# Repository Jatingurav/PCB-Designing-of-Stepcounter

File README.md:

# PCB-Designing-of-Stepcounter
I have created the circuit diagram for a Step Counter system, integrating ATtiny85 IC with MPU6050 Accelerometer & Gyroscope, and an OLED Display Module. I have developed a Multi-Layer PCB layout and developed the footprints of the components and generated Gerber files using KiCad software.

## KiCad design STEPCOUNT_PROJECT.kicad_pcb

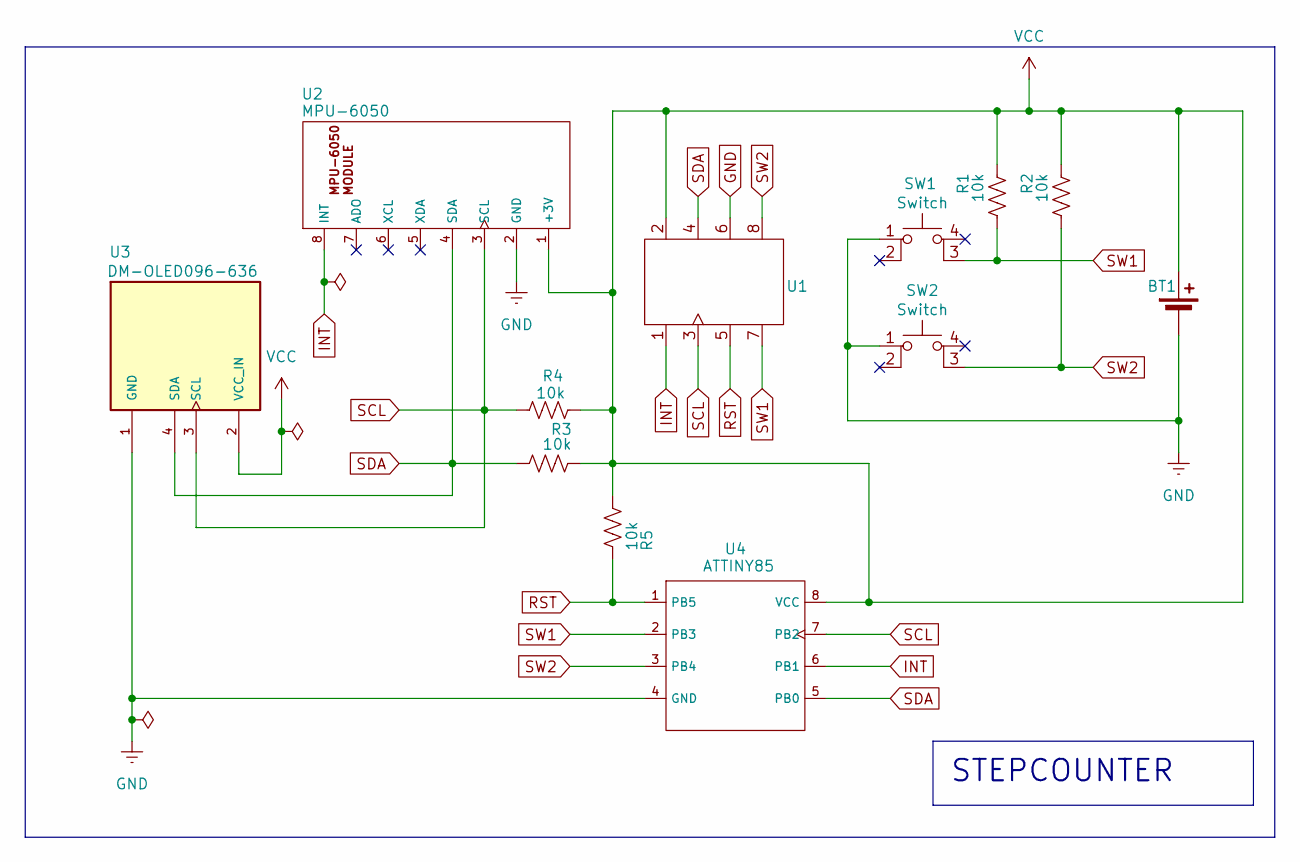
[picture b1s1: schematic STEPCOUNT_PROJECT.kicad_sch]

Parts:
BT1: Battery_Cell; Battery_Panasonic_CR2032-HFN_Horizontal_CircularHoles
R1, R2, R3, R4, R5: 10k; R_Axial_DIN0204_L3.6mm_D1.6mm_P1.90mm_Vertical
SW1, SW2: Switch; Push_E-Switch_KS01Q01
U1: HEADER
U2: MPU-6050; MPU-6050_MODULE
U3: DM-OLED096-636; OLED_DISPLAY; PARTREV 2018-09-10
U4: ATTINY85; ATTINY85_MODULE

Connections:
GND: BT1.2 (-), SW1.1, SW2.1, U1.6, U2.2 (GND), U3.1 (GND), U4.4 (GND)
INT: U1.1, U2.8 (INT), U4.6 (PB1)
RST: R5.2, U1.5, U4.1 (PB5)
SCL: R4.1, U1.3, U2.3 (SCL), U3.3 (SCL), U4.7 (PB2)
SDA: R3.1, U1.4, U2.4 (SDA), U3.4 (SDA), U4.5 (PB0)
SW1: R1.1, SW1.3 (K), U1.7, U4.2 (PB3)
SW2: R2.1, SW2.3 (K), U1.8, U4.3 (PB4)
VCC: BT1.1 (+), R1.2, R2.2, R3.2, R4.2, R5.1, U1.2, U2.1 (+3V), U3.2 (VCC_IN), U4.8 (VCC)

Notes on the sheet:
STEPCOUNTER

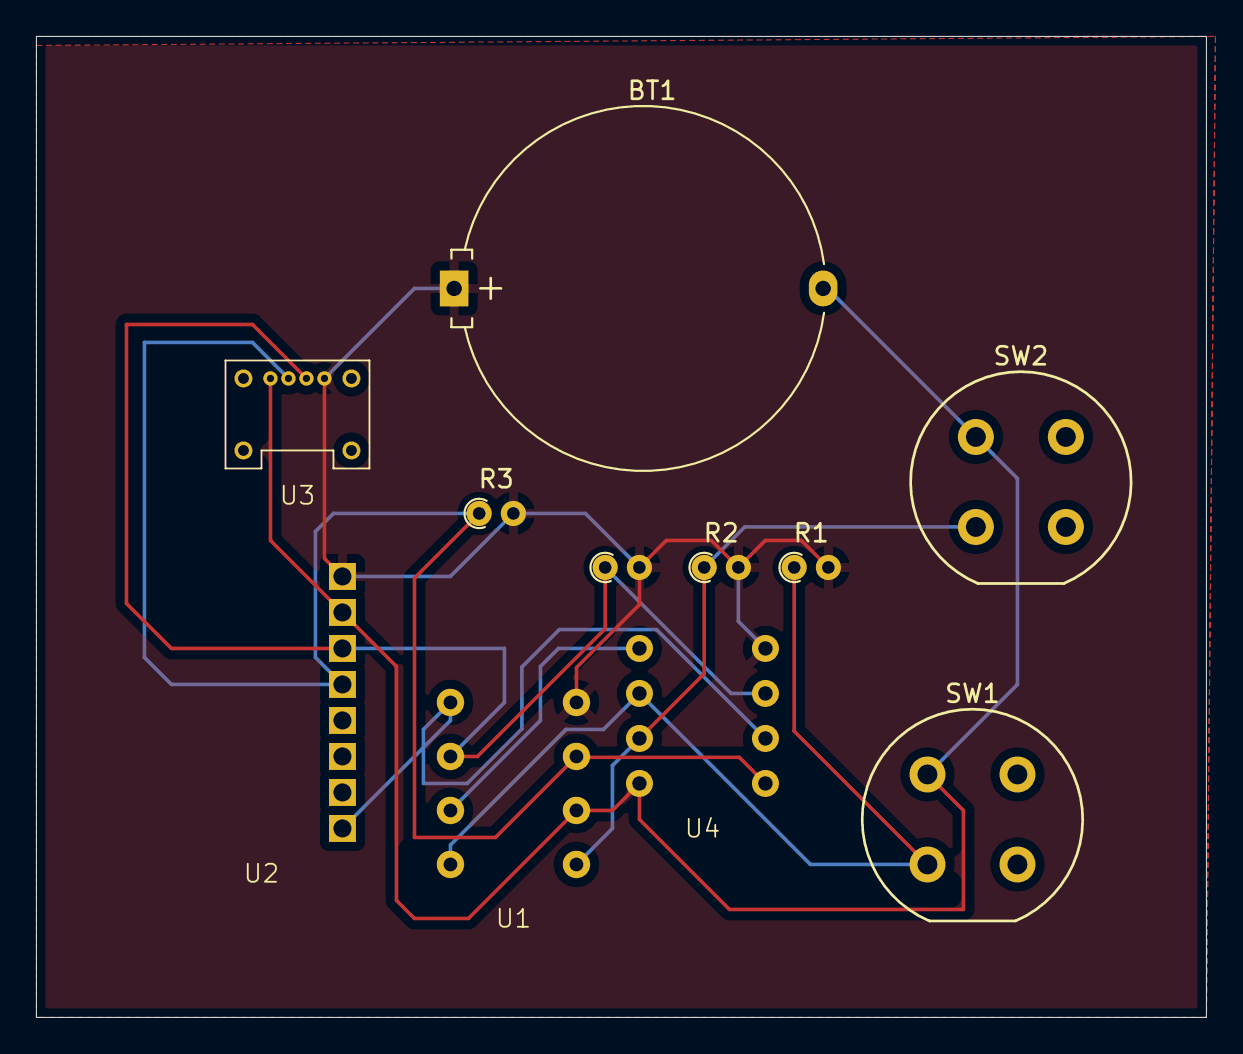
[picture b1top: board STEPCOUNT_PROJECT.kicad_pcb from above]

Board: 2 copper layers, 65.0 x 54.5 mm, 11 parts (0 on the bottom side), 8 nets.

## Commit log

2024-05-22 Create Stepcounter Project
